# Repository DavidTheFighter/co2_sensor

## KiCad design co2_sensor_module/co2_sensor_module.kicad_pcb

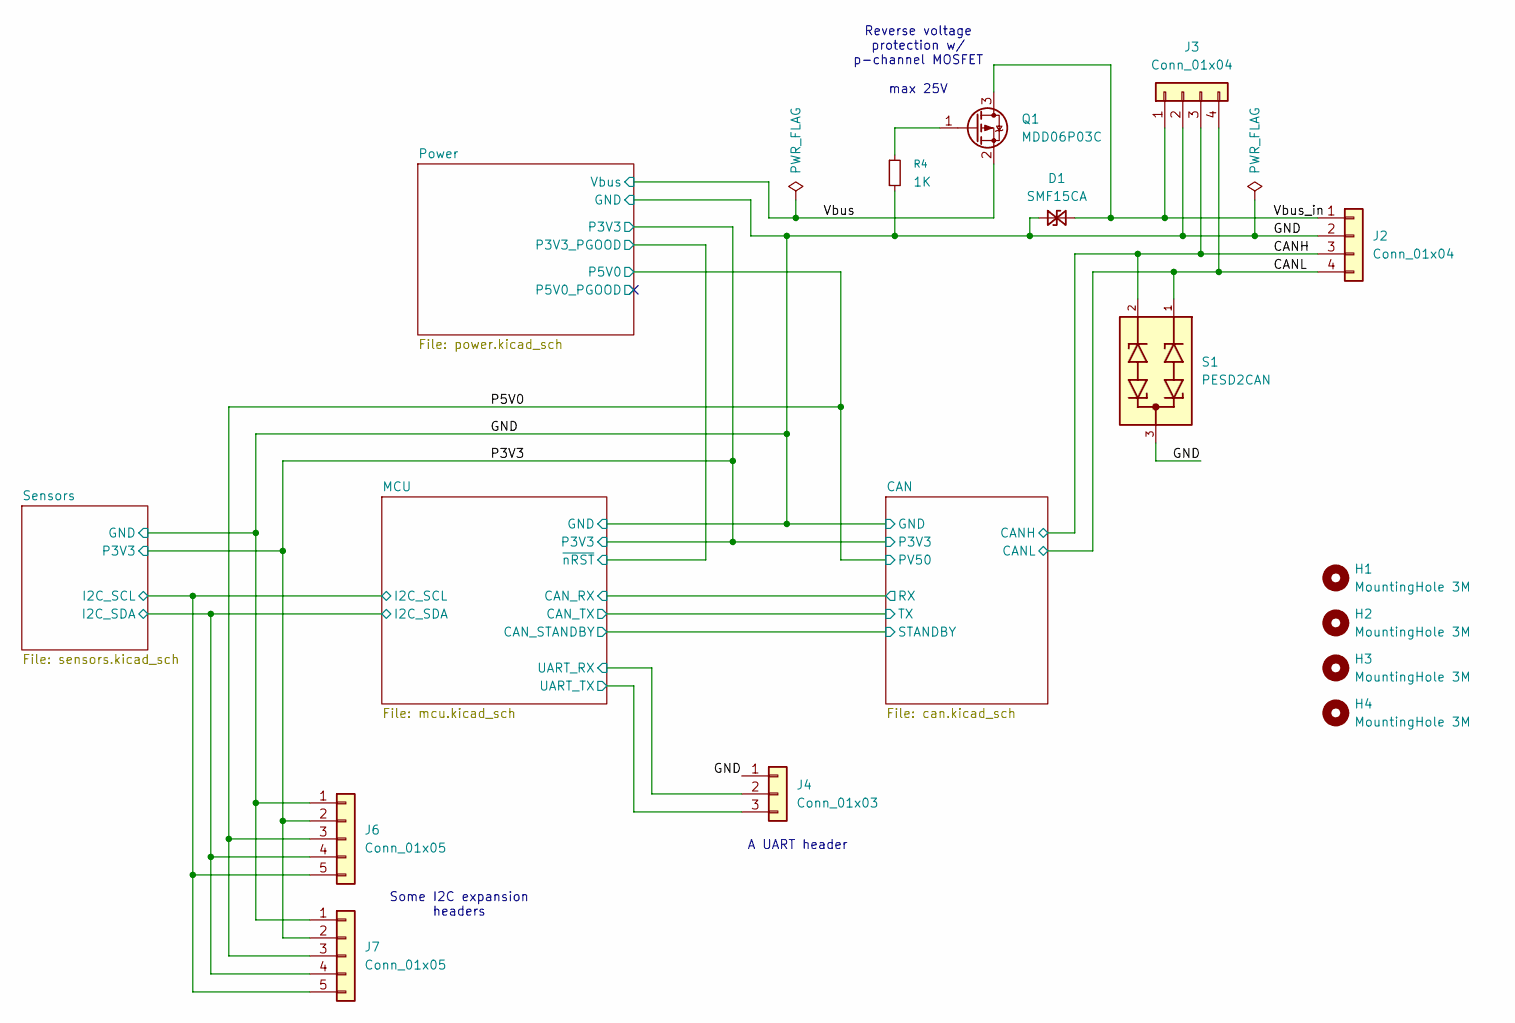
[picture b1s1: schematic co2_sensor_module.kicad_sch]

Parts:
D1: SMF15CA; D_SOD-123F; LCSC C19077510
H1, H2, H3, H4: MountingHole 3M; MountingHole_3.2mm_M3
J2, J3: Conn_01x04; WAGO-250-104
J4: Conn_01x03; PinHeader_1x03_P2.54mm_Vertical
J6, J7: Conn_01x05; PinHeader_1x05_P2.54mm_Vertical
Q1: MDD06P03C; SOT-23; LCSC C53069233
R4: 1K; R_0603_1608Metric; LCSC C21190
S1: PESD2CAN; SOT-23; MPN PESD2CAN,215; LCSC C2687131

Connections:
/CANH: J2.3, J3.3, S1.2; also elsewhere on the board
/CANL: J2.4, J3.4, S1.1; also elsewhere on the board
/GND: D1.1 (A1), J2.2, J3.2, J4.1, J6.1, J7.1, R4.2, S1.3; also elsewhere on the board
/MCU/I2C_SCL: J6.5, J7.5; also elsewhere on the board
/MCU/I2C_SDA: J6.4, J7.4; also elsewhere on the board
/MCU/UART_RX: J4.2; also elsewhere on the board
/MCU/UART_TX: J4.3; also elsewhere on the board
/P3V3: J6.2, J7.2; also elsewhere on the board
/P5V0: J6.3, J7.3; also elsewhere on the board
/Vbus: Q1.2 (S); also elsewhere on the board
/Vbus_in: D1.2 (A2), J2.1, J3.1, Q1.3 (D)
unnamed: Q1.1 (G), R4.1

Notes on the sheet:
Some I2C expansion headers
Reverse voltage protection w/ p-channel MOSFET max 25V
A UART header

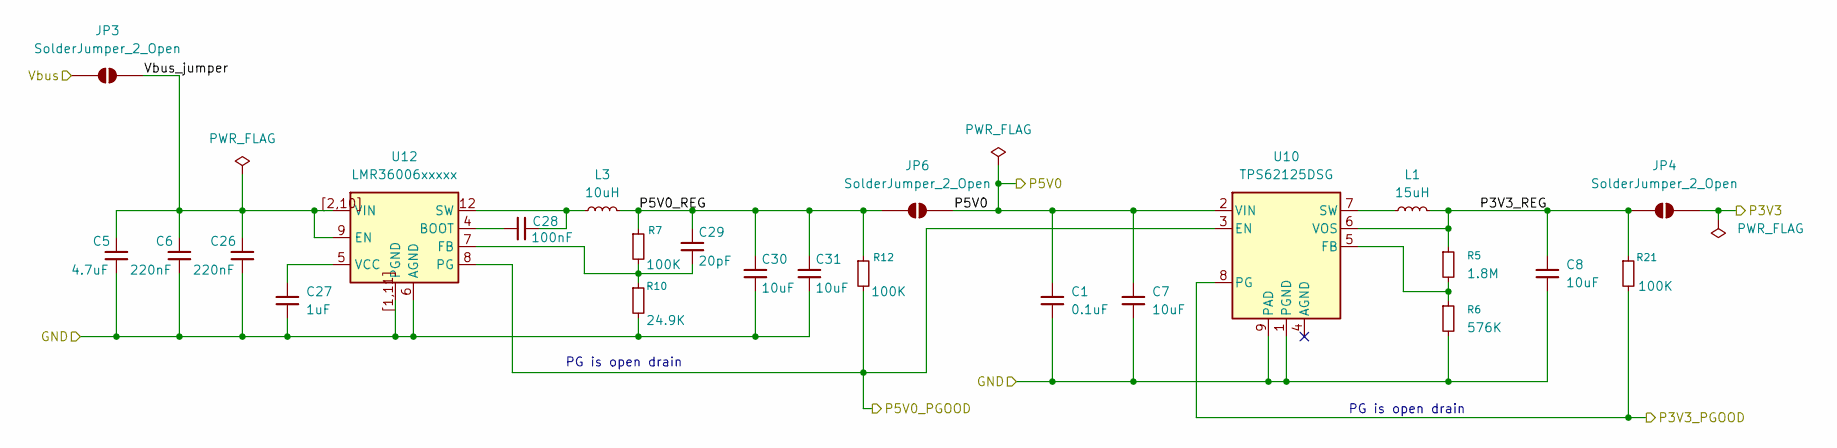
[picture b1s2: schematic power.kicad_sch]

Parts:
C1: 0.1uF; C_0603_1608Metric; LCSC C14663
C5: 4.7uF; C_1206_3216Metric; LCSC C29823
C6, C26: 220nF; C_0805_2012Metric; LCSC C5378
C7, C8, C30, C31: 10uF; C_0805_2012Metric; LCSC C15850
C27: 1uF; C_0603_1608Metric; LCSC C15849
C28: 100nF; C_0402_1005Metric; LCSC C1525
C29: 20pF; C_0402_1005Metric; LCSC C1554
JP3, JP4, JP6: SolderJumper_2_Open; SolderJumper-2_P1.3mm_Open_TrianglePad1.0x1.5mm
L1: 15uH; L_1008_2520Metric; LCSC C49073579
L3: 10uH; L_1008_2520Metric; LCSC C48783302
R5: 1.8M; R_0402_1005Metric; LCSC C2933079
R6: 576K; R_0402_1005Metric; LCSC C2085028
R7, R12, R21: 100K; R_0402_1005Metric; LCSC C25741
R10: 24.9K; R_0402_1005Metric; LCSC C138027
U10: TPS62125DSG; Texas_DSG0008A_WSON-8-1EP_2x2mm_P0.5mm_EP0.9x1.6mm_ThermalV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; LCSC C324076
U12: LMR36006xxxxx; LCSC C2862581

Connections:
/GND: C1.2, C5.2, C6.2, C7.2, C8.2, C26.2, C27.2, C30.2, C31.2, R6.2, R10.2, U10.1 (PGND), U10.9 (PAD), U12.1 (PGND), U12.6 (AGND), U12.11 (PGND), U12.[1,11] (PGND); also elsewhere on the board
/MCU/~nRST: R21.2, U10.8 (PG); also elsewhere on the board
/P3V3: JP4.2 (B); also elsewhere on the board
/P5V0: C1.1, C7.1, JP6.2 (B), U10.2 (VIN); also elsewhere on the board
/Power/P3V3_REG: C8.1, JP4.1 (A), L1.2, R5.1, R21.1, U10.6 (VOS)
/Power/P5V0_PGOOD: R12.2, U10.3 (EN), U12.8 (PG)
/Power/P5V0_REG: C29.1, C30.1, C31.1, JP6.1 (A), L3.2, R7.1, R12.1
/Power/Vbus_jumper: C5.1, C6.1, C26.1, JP3.1 (A), U12.2 (VIN), U12.9 (EN), U12.10 (VIN), U12.[2,10] (VIN)
/Vbus: JP3.2 (B); also elsewhere on the board
unnamed: R5.2, R6.1, U10.5 (FB)
unnamed: L1.1, U10.7 (SW)
unnamed: C28.1, U12.4 (BOOT)
unnamed: C29.2, R7.2, R10.1, U12.7 (FB)
unnamed: C28.2, L3.1, U12.12 (SW)
unnamed: C27.1, U12.5 (VCC)

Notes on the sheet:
PG is open drain

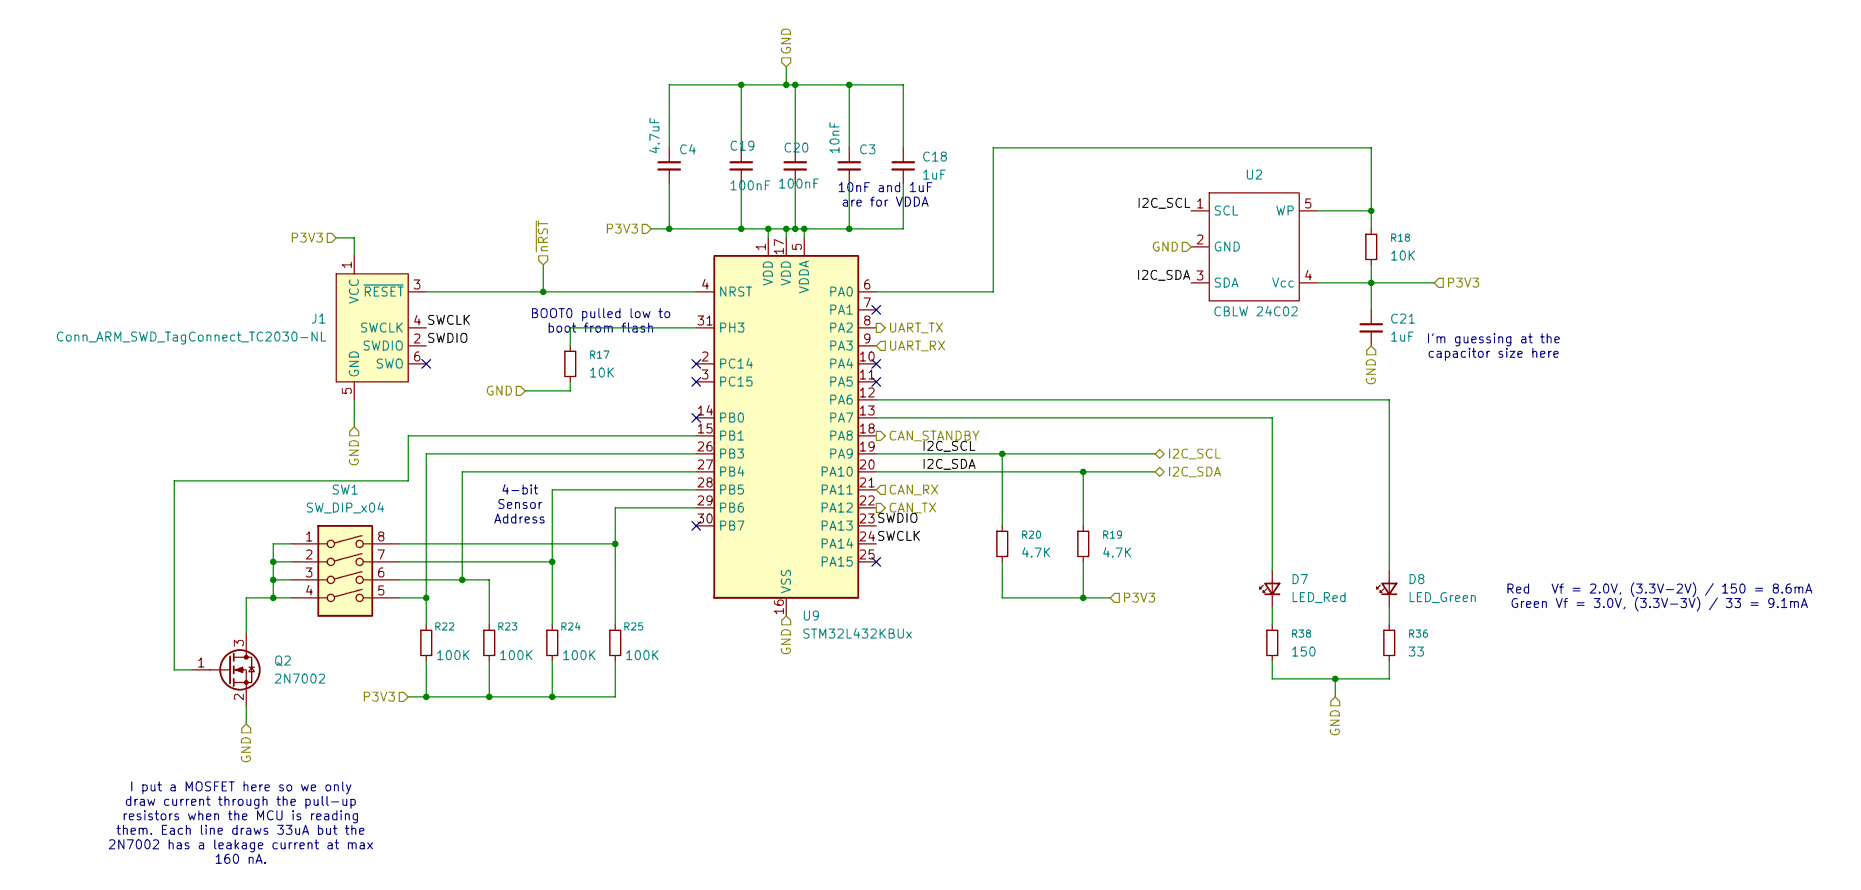
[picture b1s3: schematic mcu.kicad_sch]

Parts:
C3: 10nF; C_0402_1005Metric; LCSC C15195
C4: 4.7uF; C_0603_1608Metric; LCSC C19666
C18, C21: 1uF; C_0603_1608Metric; LCSC C15849
C19, C20: 100nF; C_0402_1005Metric; LCSC C1525
D7: LED_Red; LED_0805_2012Metric; LCSC C84256
D8: LED_Green; LED_0805_2012Metric; LCSC C2297
J1: Conn_ARM_SWD_TagConnect_TC2030-NL; Tag-Connect_TC2030-IDC-NL_2x03_P1.27mm_Vertical
Q2: 2N7002; SOT-23; LCSC C8545
R17, R18: 10K; R_0402_1005Metric; LCSC C25744
R19, R20: 4.7K; R_0402_1005Metric; LCSC C25900
R22, R23, R24, R25: 100K; R_0402_1005Metric; LCSC C25741
R36: 33; R_0603_1608Metric; LCSC C23140
R38: 150; R_0603_1608Metric; LCSC C22808
SW1: SW_DIP_x04; SW_DIP_SPSTx04_Slide_9.78x12.34mm_W7.62mm_P2.54mm
U2: CBLW 24C02; SOT-23-5; LCSC C18723540
U9: STM32L432KBUx; QFN-32-1EP_5x5mm_P0.5mm_EP3.45x3.45mm; LCSC C2928224

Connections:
/CAN/RX: U9.21 (PA11); also elsewhere on the board
/CAN/STANDBY: U9.18 (PA8); also elsewhere on the board
/CAN/TX: U9.22 (PA12); also elsewhere on the board
/GND: C3.1, C4.1, C18.1, C19.1, C20.1, C21.2, J1.5 (GND), Q2.2 (S), R17.2, R36.2, R38.2, U2.2 (GND), U9.16 (VSS), U9.32 (VSS), U9.33 (VSS); also elsewhere on the board
/MCU/I2C_SCL: R20.1, U2.1 (SCL), U9.19 (PA9); also elsewhere on the board
/MCU/I2C_SDA: R19.1, U2.3 (SDA), U9.20 (PA10); also elsewhere on the board
/MCU/SWCLK: J1.4 (SWCLK), U9.24 (PA14)
/MCU/SWDIO: J1.2 (SWDIO), U9.23 (PA13)
/MCU/UART_RX: U9.9 (PA3); also elsewhere on the board
/MCU/UART_TX: U9.8 (PA2); also elsewhere on the board
/MCU/~nRST: J1.3 (~RESET), U9.4 (NRST); also elsewhere on the board
/P3V3: C3.2, C4.2, C18.2, C19.2, C20.2, C21.1, J1.1 (VCC), R18.2, R19.2, R20.2, R22.2, R23.2, R24.2, R25.2, U2.4 (Vcc), U9.1 (VDD), U9.5 (VDDA), U9.17 (VDD); also elsewhere on the board
unnamed: D7.2 (A), U9.13 (PA7)
unnamed: D7.1 (K), R38.1
unnamed: D8.2 (A), U9.12 (PA6)
unnamed: D8.1 (K), R36.1
unnamed: Q2.3 (D), SW1.1, SW1.2, SW1.3, SW1.4
unnamed: Q2.1 (G), U9.15 (PB1)
unnamed: R18.1, U2.5 (WP), U9.6 (PA0)
unnamed: R22.1, SW1.5, U9.26 (PB3)
unnamed: R23.1, SW1.6, U9.27 (PB4)
unnamed: R24.1, SW1.7, U9.28 (PB5)
unnamed: R25.1, SW1.8, U9.29 (PB6)
unnamed: R17.1, U9.31 (PH3)

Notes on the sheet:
I put a MOSFET here so we only draw current through the pull-up resistors when the MCU is reading them. Each line draws 33uA but the 2N7002 has a leakage current at max 160 nA.
Red Vf = 2.0V, (3.3V-2V) / 150 = 8.6mA Green Vf = 3.0V, (3.3V-3V) / 33 = 9.1mA
BOOT0 pulled low to boot from flash
I'm guessing at the capacitor size here
10nF and 1uF are for VDDA
4-bit Sensor Address

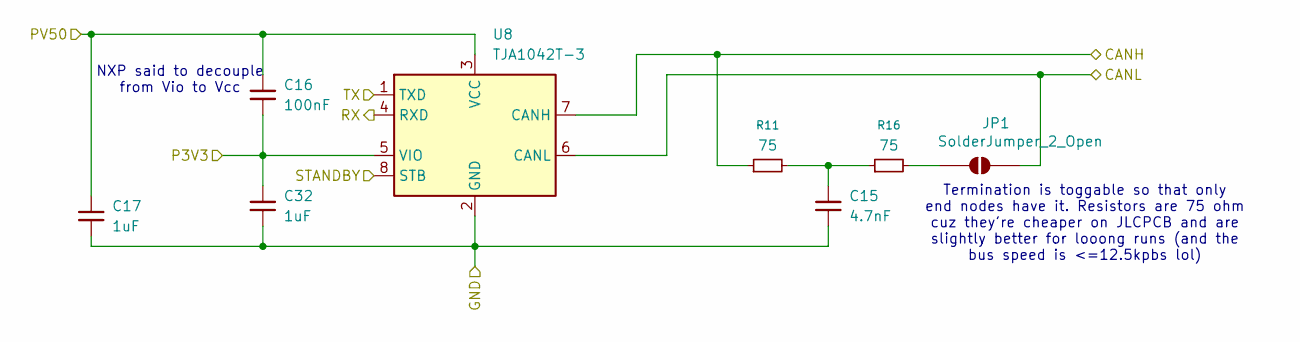
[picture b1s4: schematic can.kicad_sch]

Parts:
C15: 4.7nF; C_0805_2012Metric; LCSC C1744
C16: 100nF; C_0402_1005Metric; LCSC C1525
C17, C32: 1uF; C_0603_1608Metric; LCSC C15849
JP1: SolderJumper_2_Open; SolderJumper-2_P1.3mm_Open_TrianglePad1.0x1.5mm
R11, R16: 75; R_0603_1608Metric; LCSC C4275
U8: TJA1042T-3; SOIC-8_3.9x4.9mm_P1.27mm; LCSC C132227

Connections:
/CAN/RX: U8.4 (RXD); also elsewhere on the board
/CAN/STANDBY: U8.8 (STB); also elsewhere on the board
/CAN/TX: U8.1 (TXD); also elsewhere on the board
/CANH: R11.1, U8.7 (CANH); also elsewhere on the board
/CANL: JP1.2 (B), U8.6 (CANL); also elsewhere on the board
/GND: C15.2, C17.2, C32.2, U8.2 (GND); also elsewhere on the board
/P3V3: C16.2, C32.1, U8.5 (VIO); also elsewhere on the board
/P5V0: C16.1, C17.1, U8.3 (VCC); also elsewhere on the board
unnamed: C15.1, R11.2, R16.1
unnamed: JP1.1 (A), R16.2

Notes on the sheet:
Termination is toggable so that only end nodes have it. Resistors are 75 ohm cuz they're cheaper on JLCPCB and are slightly better for looong runs (and the bus speed is <=12.5kpbs lol)
NXP said to decouple from Vio to Vcc

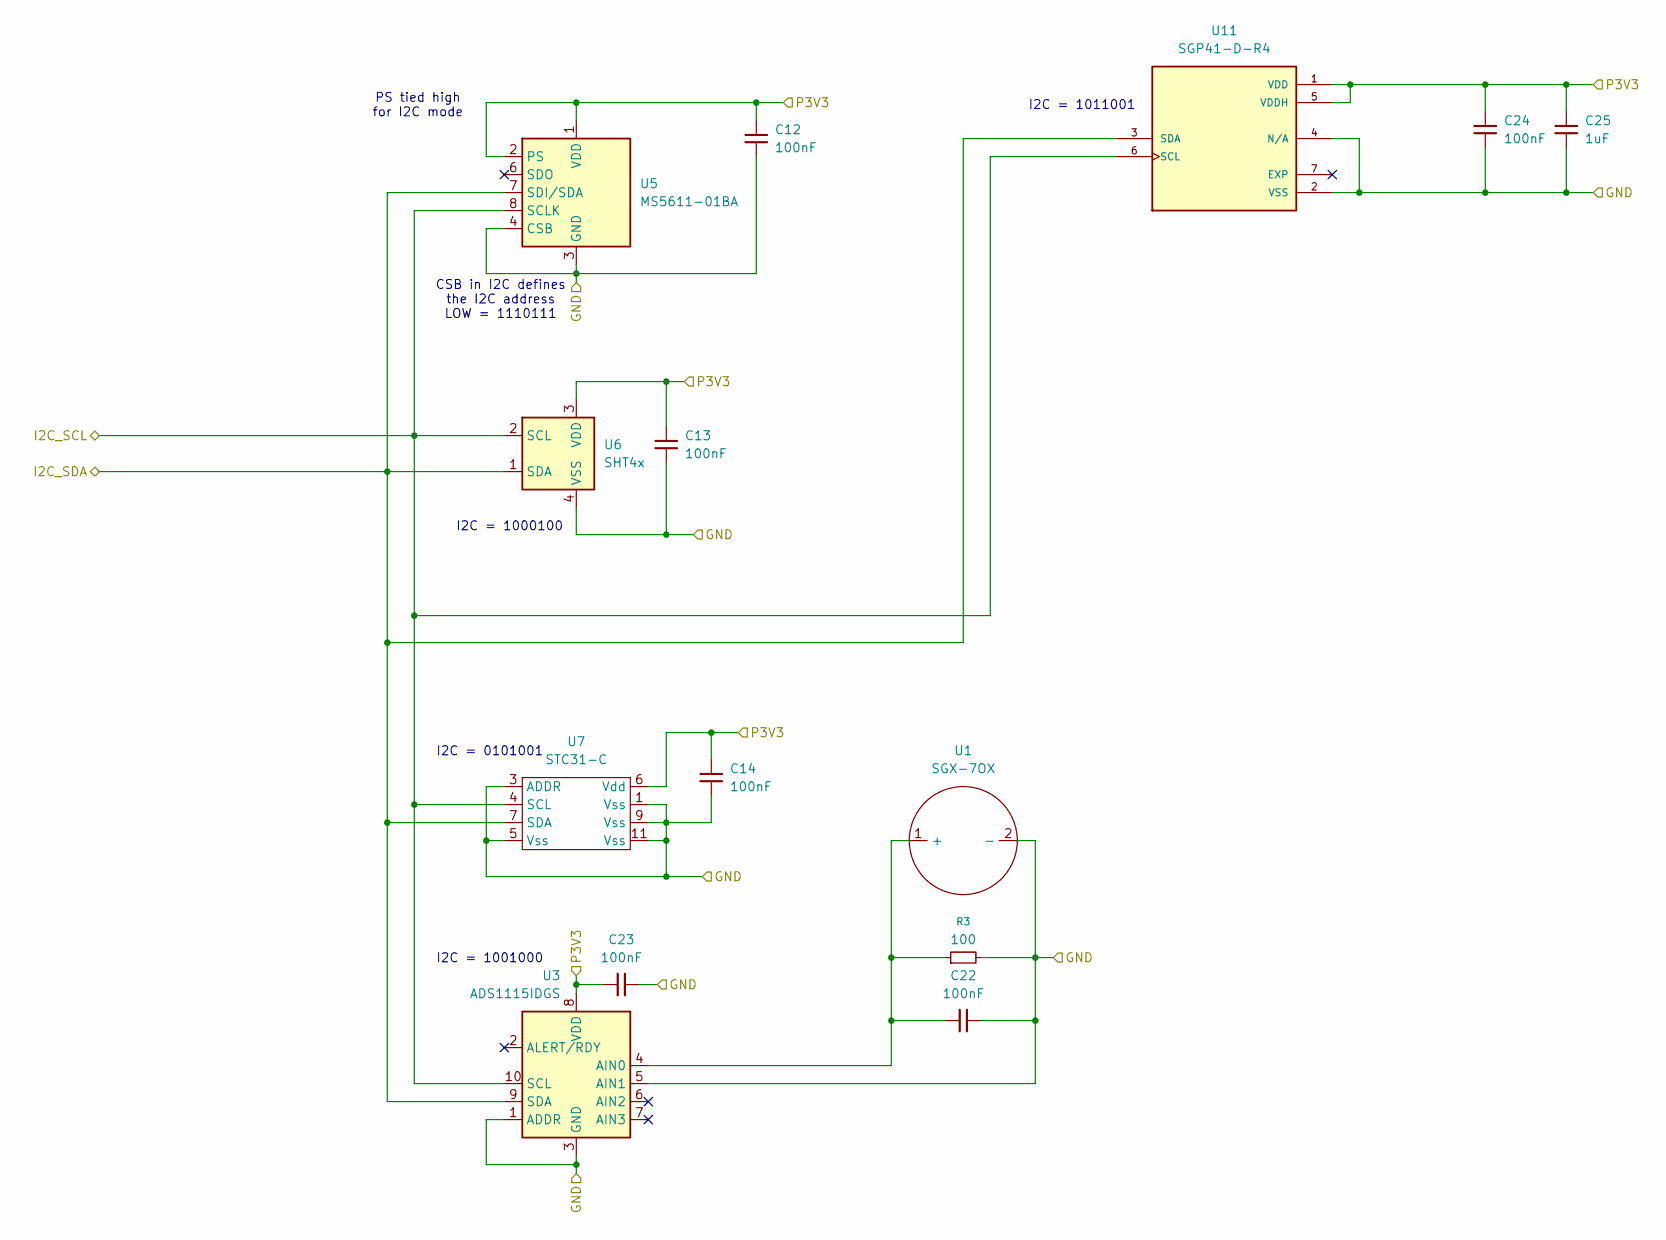
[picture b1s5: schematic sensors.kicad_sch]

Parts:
C12, C13, C14, C22, C23, C24: 100nF; C_0402_1005Metric; LCSC C1525
C25: 1uF; C_0603_1608Metric; LCSC C15849
R3: 100; R_0603_1608Metric; LCSC C122970
U1: SGX-7OX
U3: ADS1115IDGS; TSSOP-10_3x3mm_P0.5mm; LCSC C37593
U5: MS5611-01BA; LGA-8_3x5mm_P1.25mm; LCSC C15639
U6: SHT4x; Sensirion_DFN-4_1.5x1.5mm_P0.8mm_SHT4x_NoCentralPad; LCSC C2909890
U7: STC31-C; STC31-C-R5; LCSC C22396918
U11: SGP41-D-R4; XDCR_SGP41-D-R4; LCSC C3659325

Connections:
/GND: C12.2, C13.2, C14.2, C22.2, C23.2, C24.2, C25.2, R3.2, U1.2 (-), U3.1 (ADDR), U3.3 (GND), U3.5 (AIN1), U5.3 (GND), U5.4 (CSB), U5.5 (CSB), U6.4 (VSS), U7.1 (Vss), U7.3 (ADDR), U7.5 (Vss), U7.9 (Vss), U7.11 (Vss), U11.2 (VSS), U11.4 (N/A); also elsewhere on the board
/MCU/I2C_SCL: U3.10 (SCL), U5.8 (SCLK), U6.2 (SCL), U7.4 (SCL), U11.6 (SCL); also elsewhere on the board
/MCU/I2C_SDA: U3.9 (SDA), U5.7 (SDI/SDA), U6.1 (SDA), U7.7 (SDA), U11.3 (SDA); also elsewhere on the board
/P3V3: C12.1, C13.1, C14.1, C23.1, C24.1, C25.1, U3.8 (VDD), U5.1 (VDD), U5.2 (PS), U6.3 (VDD), U7.6 (Vdd), U11.1 (VDD), U11.5 (VDDH); also elsewhere on the board
unnamed: C22.1, R3.1, U1.1 (+), U3.4 (AIN0)

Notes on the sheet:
I2C = 1001000
I2C = 0101001
PS tied high for I2C mode
I2C = 1011001
CSB in I2C defines the I2C address LOW = 1110111
I2C = 1000100

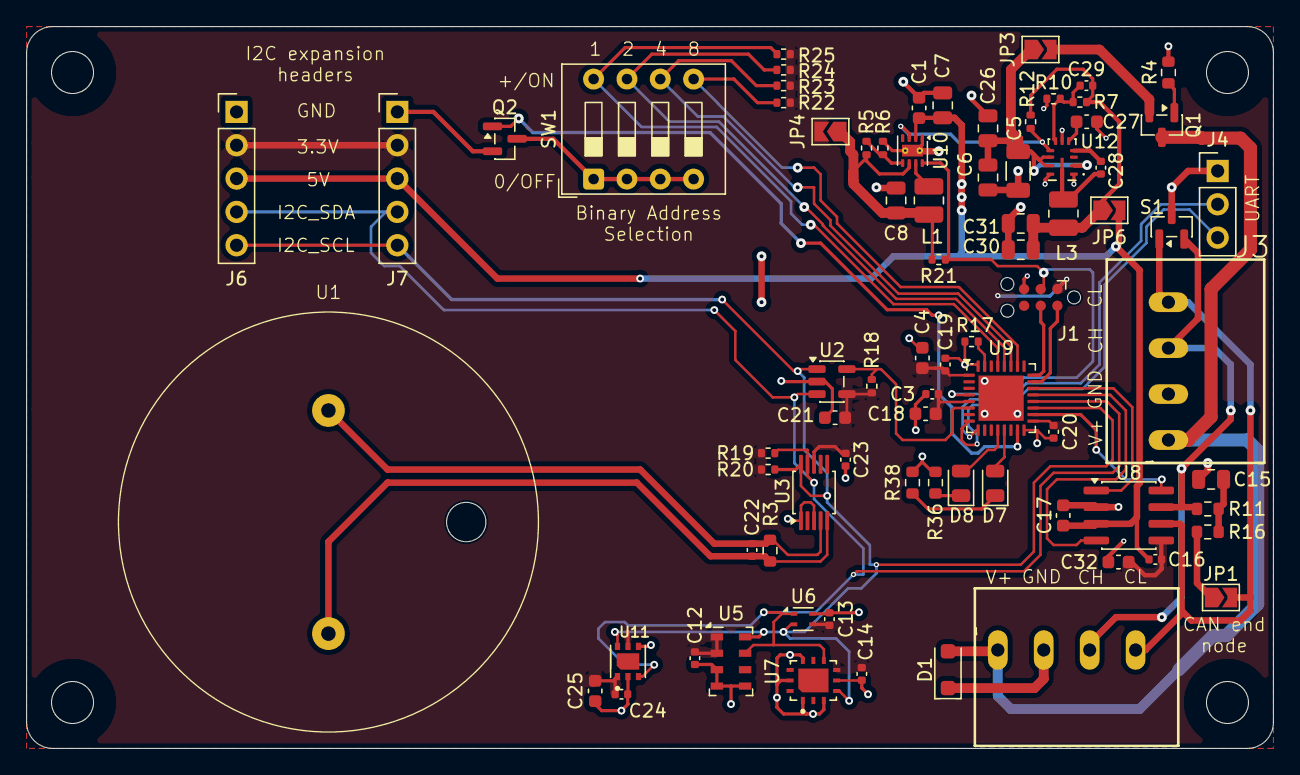
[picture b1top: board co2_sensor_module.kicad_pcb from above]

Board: 2 copper layers, 95.0 x 55.0 mm, 82 parts (0 on the bottom side), 43 nets.

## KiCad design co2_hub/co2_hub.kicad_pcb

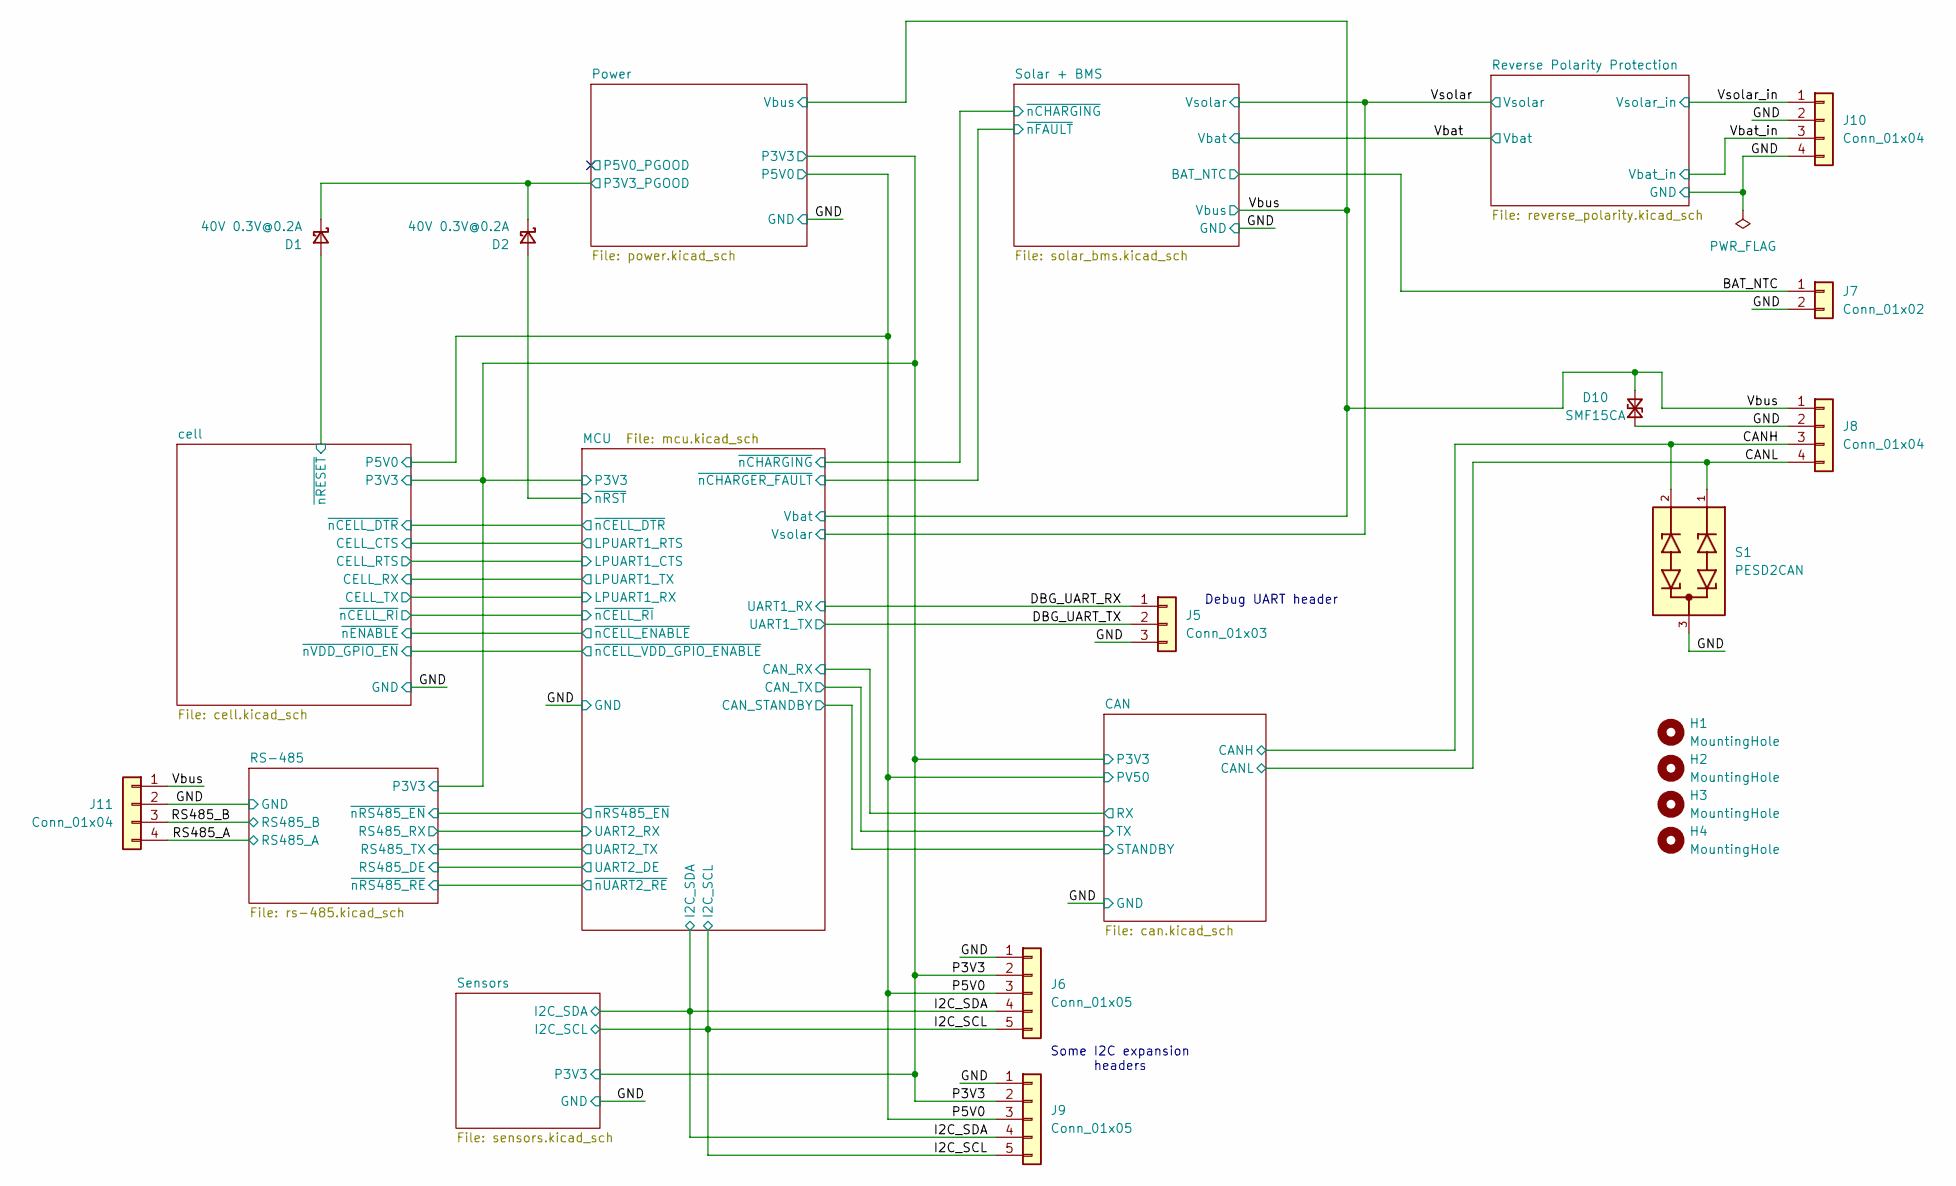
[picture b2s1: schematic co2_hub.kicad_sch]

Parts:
D1, D2: 40V 0.3V@0.2A; D_SOD-523; LCSC C135802
D10: SMF15CA; D_SOD-123F; LCSC C19077510
H1, H2, H3, H4: MountingHole; MountingHole_3.2mm_M3
J5: Conn_01x03; PinHeader_1x03_P2.54mm_Vertical
J6, J9: Conn_01x05; PinHeader_1x05_P2.54mm_Vertical
J7: Conn_01x02; JST_PH_B2B-PH-K_1x02_P2.00mm_Vertical
J8, J10, J11: Conn_01x04; WAGO-250-104
S1: PESD2CAN; SOT-23; MPN PESD2CAN,215; LCSC C2687131

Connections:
/BAT_NTC: J7.1; also elsewhere on the board
/CANH: J8.3, S1.2; also elsewhere on the board
/CANL: J8.4, S1.1; also elsewhere on the board
/DBG_UART_RX: J5.1; also elsewhere on the board
/DBG_UART_TX: J5.2; also elsewhere on the board
/I2C_SCL: J6.5, J9.5; also elsewhere on the board
/I2C_SDA: J6.4, J9.4; also elsewhere on the board
/MCU/~nRST: D2.2 (A); also elsewhere on the board
/P3V3: J6.2, J9.2; also elsewhere on the board
/P5V0: J6.3, J9.3; also elsewhere on the board
/Power/P3V3_PGOOD: D1.1 (K), D2.1 (K); also elsewhere on the board
/RS485_A: J11.4; also elsewhere on the board
/RS485_B: J11.3; also elsewhere on the board
/Vbat_in: J10.3; also elsewhere on the board
/Vbus: D10.2 (A2), J8.1, J11.1; also elsewhere on the board
/Vsolar_in: J10.1; also elsewhere on the board
/cell/~nRESET: D1.2 (A); also elsewhere on the board
GND: D10.1 (A1), J5.3, J6.1, J7.2, J8.2, J9.1, J10.2, J10.4, J11.2, S1.3; also elsewhere on the board

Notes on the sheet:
Some I2C expansion headers
Debug UART header

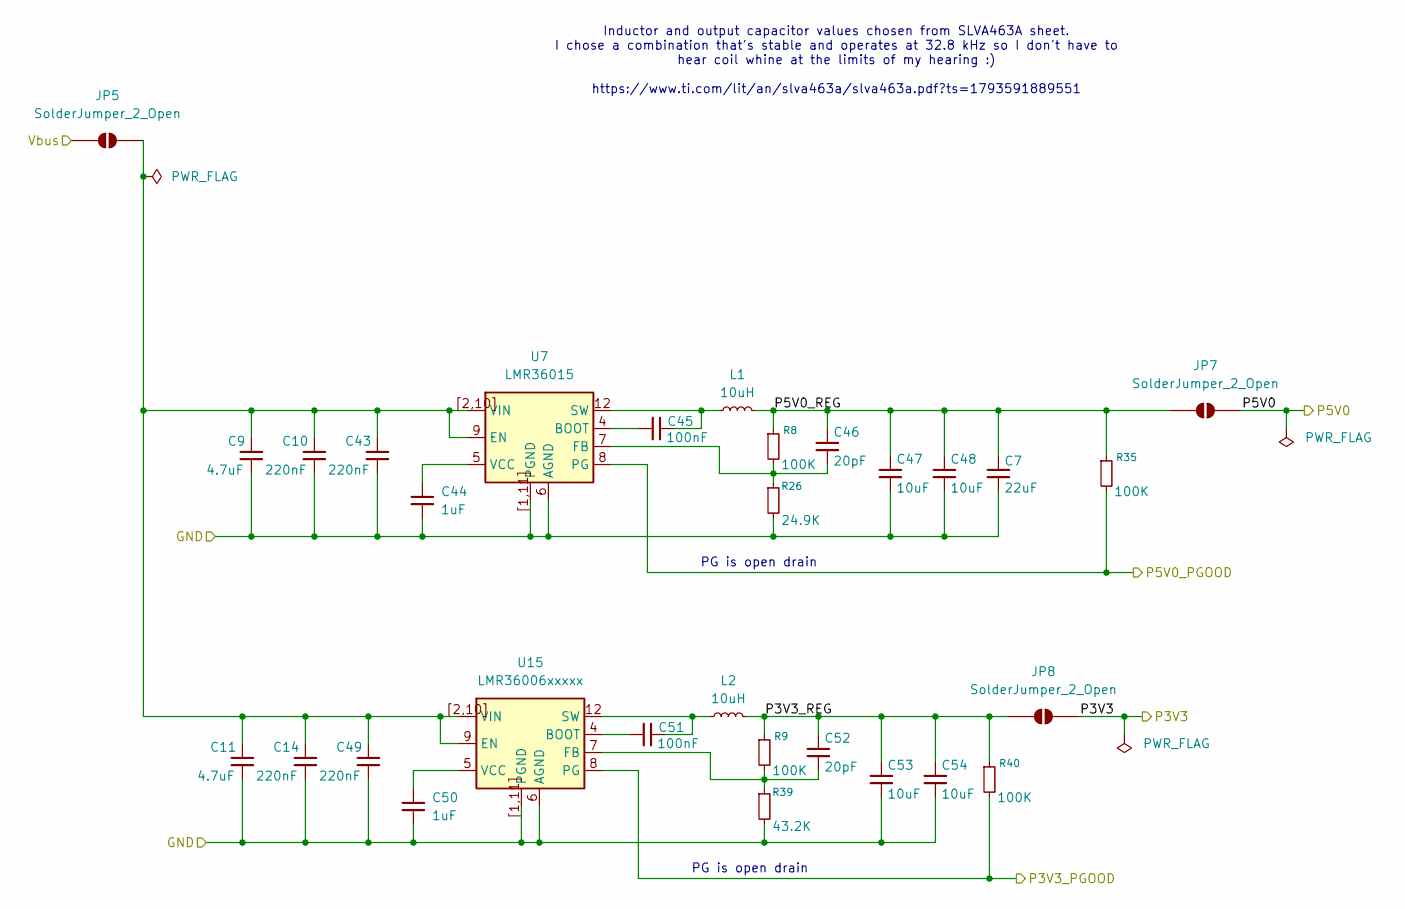
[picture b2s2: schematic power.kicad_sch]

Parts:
C7: 22uF; C_0805_2012Metric; LCSC C45783
C9, C11: 4.7uF; C_1206_3216Metric; LCSC C29823
C10, C14, C43, C49: 220nF; C_0805_2012Metric; LCSC C5378
C44, C50: 1uF; C_0603_1608Metric; LCSC C15849
C45, C51: 100nF; C_0402_1005Metric; LCSC C1525
C46, C52: 20pF; C_0402_1005Metric; LCSC C1554
C47, C48, C53, C54: 10uF; C_0805_2012Metric; LCSC C15850
JP5, JP7, JP8: SolderJumper_2_Open; SolderJumper-2_P1.3mm_Open_TrianglePad1.0x1.5mm
L1, L2: 10uH; L_Changjiang_FNR4030S; LCSC C167879
R8, R9, R35, R40: 100K; R_0402_1005Metric; LCSC C25741
R26: 24.9K; R_0402_1005Metric; LCSC C138027
R39: 43.2K; R_0402_1005Metric; LCSC C2906870
U7: LMR36015; LMR36006xxxxx; LCSC C2867810
U15: LMR36006xxxxx; LCSC C1850367

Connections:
/P3V3: JP8.2 (B); also elsewhere on the board
/P5V0: JP7.2 (B); also elsewhere on the board
/Power/P3V3_PGOOD: R40.2, U15.8 (PG); also elsewhere on the board
/Power/P3V3_REG: C52.1, C53.1, C54.1, JP8.1 (A), L2.2, R9.1, R40.1
/Power/P5V0_PGOOD: R35.2, U7.8 (PG)
/Power/P5V0_REG: C7.1, C46.1, C47.1, C48.1, JP7.1 (A), L1.2, R8.1, R35.1
/Vbus: JP5.2 (B); also elsewhere on the board
GND: C7.2, C9.2, C10.2, C11.2, C14.2, C43.2, C44.2, C47.2, C48.2, C49.2, C50.2, C53.2, C54.2, R26.2, R39.2, U7.1 (PGND), U7.6 (AGND), U7.11 (PGND), U7.[1,11] (PGND), U15.1 (PGND), U15.6 (AGND), U15.11 (PGND), U15.[1,11] (PGND); also elsewhere on the board
unnamed: C9.1, C10.1, C11.1, C14.1, C43.1, C49.1, JP5.1 (A), U7.2 (VIN), U7.9 (EN), U7.10 (VIN), U7.[2,10] (VIN), U15.2 (VIN), U15.9 (EN), U15.10 (VIN), U15.[2,10] (VIN)
unnamed: C45.1, U7.4 (BOOT)
unnamed: C46.2, R8.2, R26.1, U7.7 (FB)
unnamed: C45.2, L1.1, U7.12 (SW)
unnamed: C44.1, U7.5 (VCC)
unnamed: C51.1, U15.4 (BOOT)
unnamed: C52.2, R9.2, R39.1, U15.7 (FB)
unnamed: C51.2, L2.1, U15.12 (SW)
unnamed: C50.1, U15.5 (VCC)

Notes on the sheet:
PG is open drain
Inductor and output capacitor values chosen from SLVA463A sheet. I chose a combination that's stable and operates at 32.8 kHz so I don't have to hear coil whine at the limits of my hearing :) https://www.ti.com/lit/an/slva463a/slva463a.pdf?ts=1793591889551

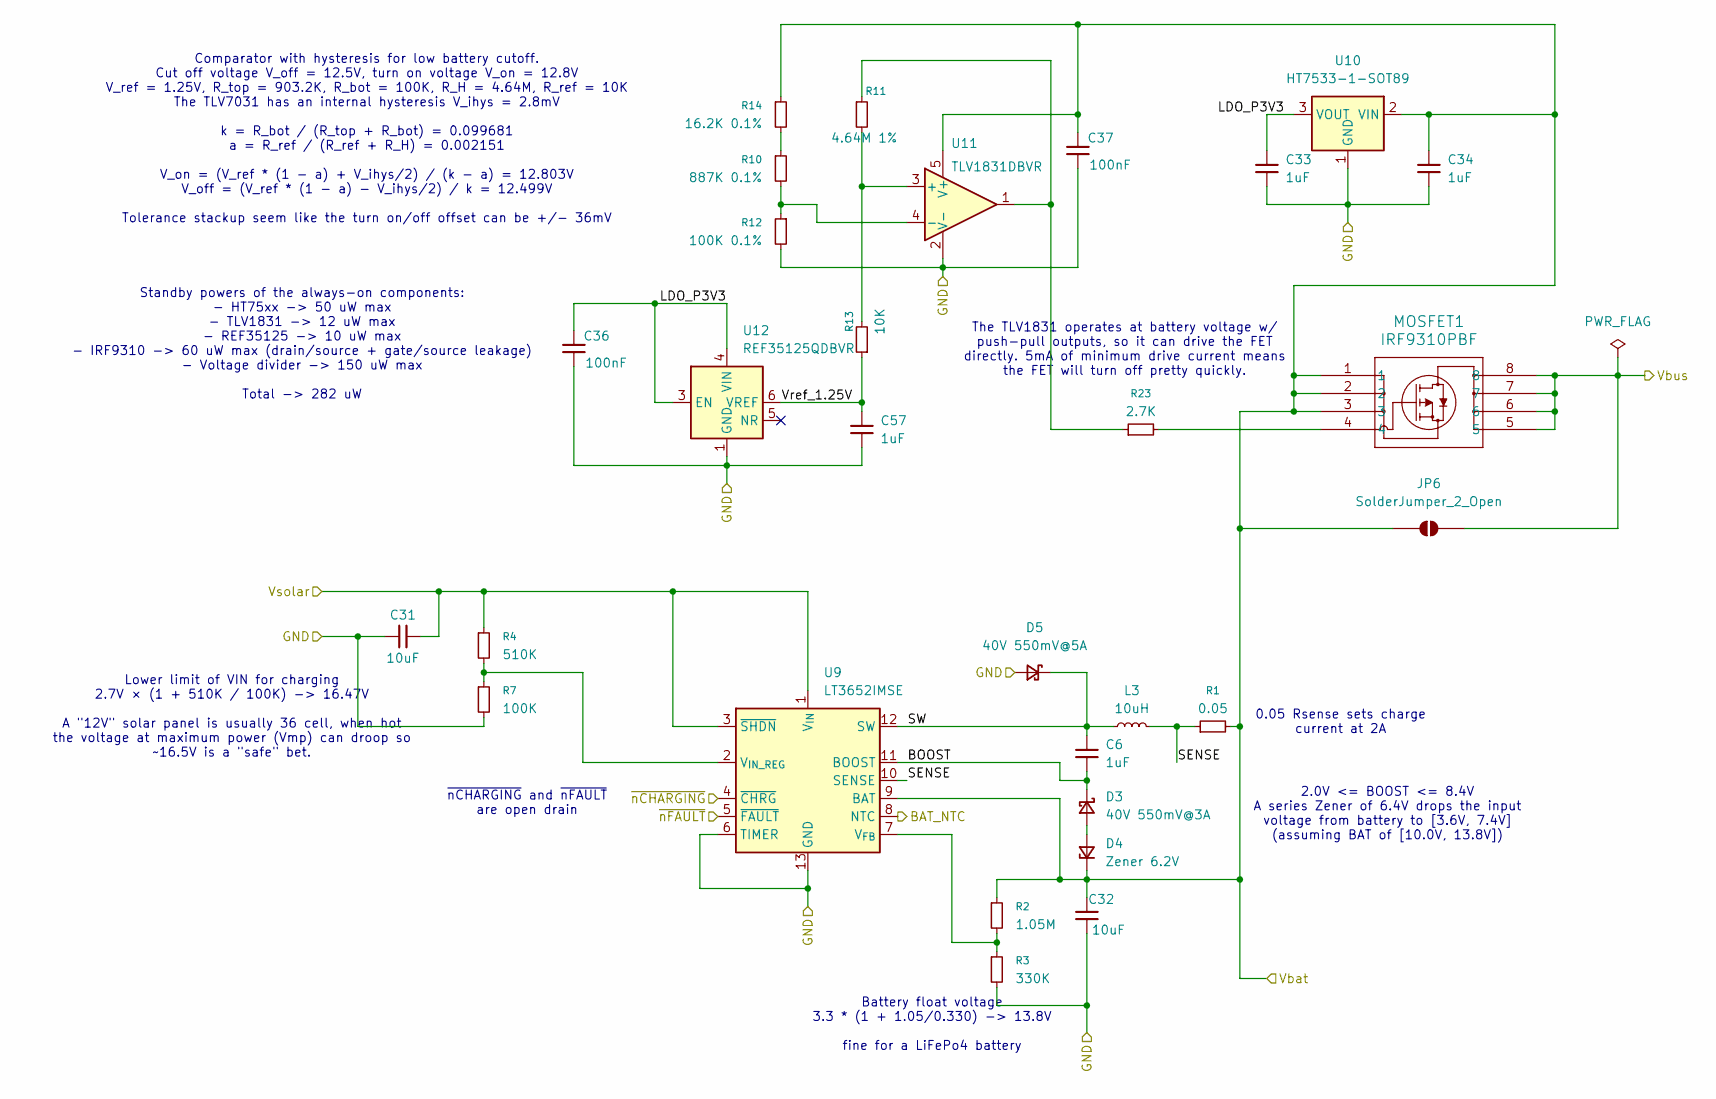
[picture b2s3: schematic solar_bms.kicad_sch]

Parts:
C6: 1uF; C_1206_3216Metric; LCSC C1848
C31, C32: 10uF; C_1206_3216Metric; LCSC C13585
C33, C34, C57: 1uF; C_0603_1608Metric; LCSC C15849
C36, C37: 100nF; C_0402_1005Metric; LCSC C1525
D3: 40V 550mV@3A; D_SMA; LCSC C8678
D4: Zener 6.2V; D_SOD-123; LCSC C22435091
D5: 40V 550mV@5A; D_SMA; LCSC C22452
JP6: SolderJumper_2_Open; SolderJumper-2_P1.3mm_Open_TrianglePad1.0x1.5mm
L3: 10uH; L_7.3x7.3_H4.5; LCSC C19268627
MOSFET1: IRF9310PBF; SO-8_3.9x4.9mm_P1.27mm; LCSC C5236693
R1: 0.05; R_1206_3216Metric; LCSC C7467249
R2: 1.05M; R_0603_1608Metric; LCSC C5126052
R3: 330K; R_0603_1608Metric; LCSC C23137
R4: 510K; R_0603_1608Metric; LCSC C23192
R7: 100K; R_0603_1608Metric; LCSC C25803
R10: 887K 0.1%; R_0603_1608Metric; LCSC C2984370
R11: 4.64M 1%; R_0603_1608Metric; LCSC C482862
R12: 100K 0.1%; R_0603_1608Metric; LCSC C122538
R13: 10K; R_0402_1005Metric; LCSC C25744
R14: 16.2K 0.1%; R_0603_1608Metric; LCSC C728602
R23: 2.7K; R_0603_1608Metric; LCSC C13167
U9: LT3652IMSE; MSOP-12-1EP_3x4.039mm_P0.65mm_EP1.651x2.845mm; LCSC C671115
U10: HT7533-1-SOT89; SOT-89-3; LCSC C14289
U11: TLV1831DBVR; SOT-23-5; LCSC C22427370
U12: REF35125QDBVR; SOT-23-6; LCSC C7043252

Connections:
/BAT_NTC: U9.8 (NTC); also elsewhere on the board
/MCU/~nCHARGER_FAULT: U9.5 (~FAULT); also elsewhere on the board
/MCU/~nCHARGING: U9.4 (~CHRG); also elsewhere on the board
/Solar + BMS/BOOST: C6.2, D3.1 (K), U9.11 (BOOST)
/Solar + BMS/LDO_P3V3: C33.1, C36.1, U10.3 (VOUT), U12.3 (EN), U12.4 (VIN)
/Solar + BMS/SENSE: L3.2, R1.1, U9.10 (SENSE)
/Solar + BMS/SW: C6.1, D5.1 (K), L3.1, U9.12 (SW)
/Solar + BMS/Vref_1.25V: C57.1, R13.1, U12.6 (VREF)
/Vbat: C32.2, C34.1, C37.1, D4.1 (K), JP6.1 (A), MOSFET1.1, MOSFET1.2, MOSFET1.3, R1.2, R2.1, R14.1, U9.9 (BAT), U10.2 (VIN), U11.5 (V+); also elsewhere on the board
/Vbus: JP6.2 (B), MOSFET1.5, MOSFET1.6, MOSFET1.7, MOSFET1.8; also elsewhere on the board
/Vsolar: C31.2, R4.1, U9.1 (V_{IN}), U9.3 (~SHDN); also elsewhere on the board
GND: C31.1, C32.1, C33.2, C34.2, C36.2, C37.2, C57.2, D5.2 (A), R3.2, R7.2, R12.2, U9.6 (TIMER), U9.13 (GND), U10.1 (GND), U11.2 (V-), U12.1 (GND), U12.2 (GND); also elsewhere on the board
unnamed: D3.2 (A), D4.2 (A)
unnamed: MOSFET1.4, R23.2
unnamed: R10.1, R14.2
unnamed: R11.1, R23.1, U11.1
unnamed: R2.2, R3.1, U9.7 (V_{FB})
unnamed: R4.2, R7.1, U9.2 (V_{IN_REG})
unnamed: R11.2, R13.2, U11.3 (+)
unnamed: R10.2, R12.1, U11.4 (-)

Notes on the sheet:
Standby powers of the always-on components: - HT75xx -> 50 uW max - TLV1831 -> 12 uW max - REF35125 -> 10 uW max - IRF9310 -> 60 uW max (drain/source + gate/source leakage) - Voltage divider -> 150 uW max Total -> 282 uW
Comparator with hysteresis for low battery cutoff. Cut off voltage V_off = 12.5V, turn on voltage V_on = 12.8V V_ref = 1.25V, R_top = 903.2K, R_bot = 100K, R_H = 4.64M, R_ref = 10K The TLV7031 has an internal hysteresis V_ihys = 2.8mV k = R_bot / (R_top + R_bot) = 0.099681 a = R_ref / (R_ref + R_H)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
0.05 Rsense sets charge current at 2A
~{nCHARGING} and ~{nFAULT} are open drain
The TLV1831 operates at battery voltage w/ push-pull outputs, so it can drive the FET directly. 5mA of minimum drive current means the FET will turn off pretty quickly.
2.0V <= BOOST <= 8.4V A series Zener of 6.4V drops the input voltage from battery to [3.6V, 7.4V] (assuming BAT of [10.0V, 13.8V])
Battery float voltage 3.3 * (1 + 1.05/0.330) -> 13.8V fine for a LiFePo4 battery
Lower limit of VIN for charging 2.7V × (1 + 510K / 100K) -> 16.47V A "12V" solar panel is usually 36 cell, when hot the voltage at maximum power (Vmp) can droop so ~16.5V is a "safe" bet.
